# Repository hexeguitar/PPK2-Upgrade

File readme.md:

# PPK2 Logic Port upgrade
### Logic port upgrade add on for the Nordic Power Profiler Kit II.  

![alt text][img_features] 
![alt text][img_main] 

Copyright (c) 2022 by Piotr Zapart  
www.hexefx.com  

[img_features]: pics/ppk2_logicPortUpgrade_v2.jpg " Features" 
[img_main]: pics/ppk2lp_1.jpg "PPK2 Logic Port upgrade"

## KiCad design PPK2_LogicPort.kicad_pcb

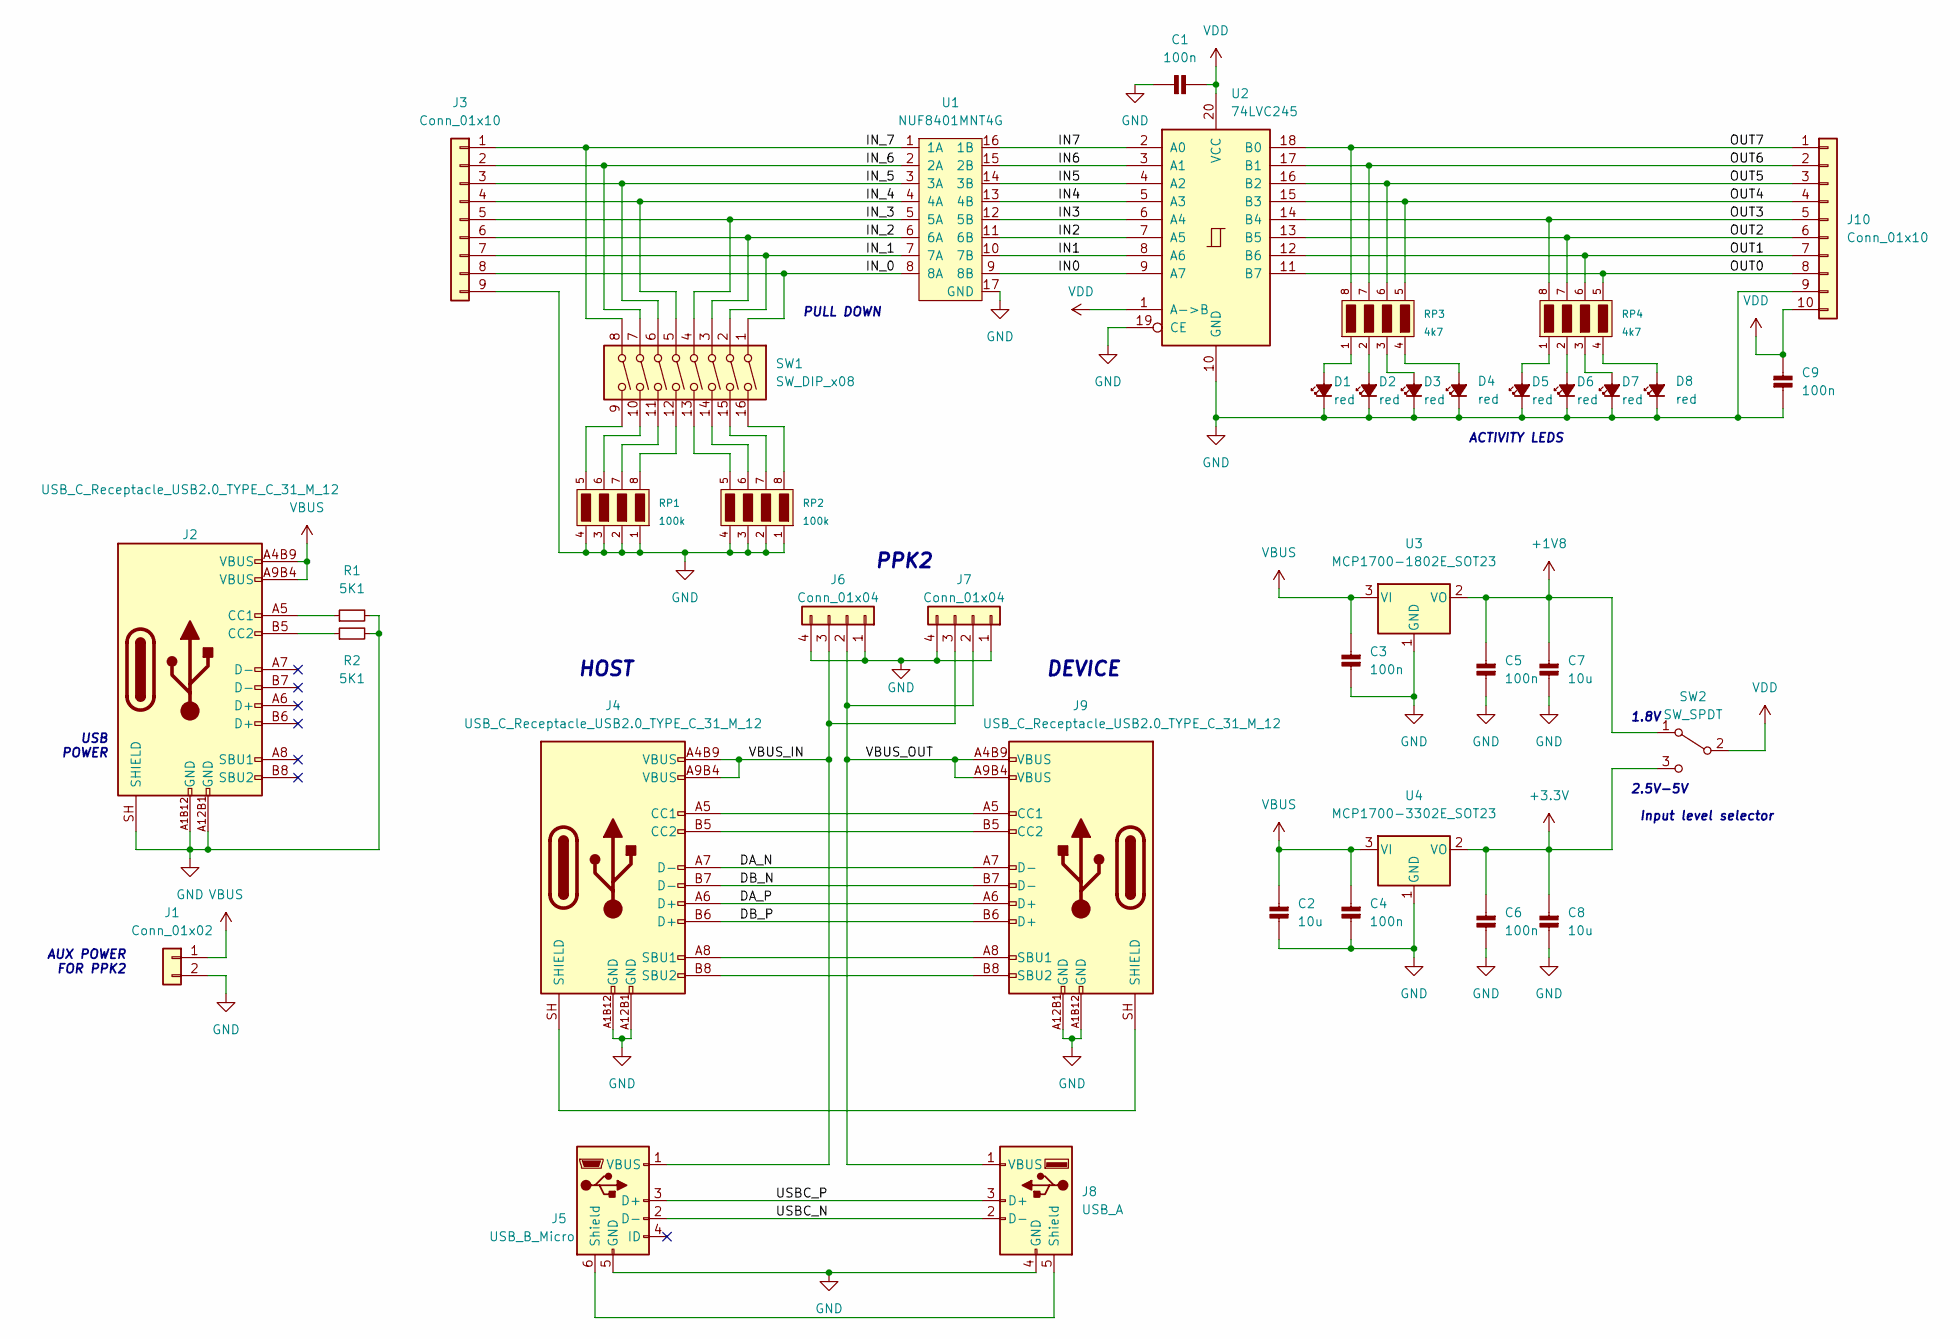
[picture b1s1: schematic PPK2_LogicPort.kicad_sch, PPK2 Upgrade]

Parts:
C1, C3, C4, C5, C6, C9: 100n; Hx_C_0603_1608Metric
C2, C7, C8: 10u; Hx_C_0805_2012Metric
D1, D2, D3, D4, D5, D6, D7, D8: red; LED_0603_1608Metric
J1: Conn_01x02; JST_PH_S2B-PH-SM4-TB_1x02-1MP_P2.00mm_Horizontal
J2, J4, J9: USB_C_Receptacle_USB2.0_TYPE_C_31_M_12; USB_C_TYPE-C-31-M-12; LCSC C283540
J3: Conn_01x10; PinHeader_1x09_P2.54mm_Horizontal
J5: USB_B_Micro; USB_Micro-B_Molex-105017-0001
J6: Conn_01x04; PinSocket_1x04_P2.54mm_Horizontal
J7: Conn_01x04; PinHeader_1x04_P2.54mm_Vertical
J8: USB_A; USB_A_Molex_67643_Horizontal
J10: Conn_01x10; PinSocket_1x10_P2.54mm_Horizontal
R1, R2: 5K1; Hx_R_0805_2012Metric
RP1, RP2: 100k; R_Array_Convex_4x0603
RP3, RP4: 4k7; R_Array_Convex_4x0603
SW1: SW_DIP_x08; SW_DIP_SPSTx08_Slide_9.78x22.5mm_W7.62mm_P2.54mm
SW2: SW_SPDT; SW_SPDT_PCM12
U1: NUF8401MNT4G; DFN-16-1EP_1.6x4mm_P0.5mm
U2: 74LVC245; TSSOP-20_4.4x6.5mm_Pitch0.65mm
U3: MCP1700-1802E_SOT23; SOT-23
U4: MCP1700-3302E_SOT23; SOT-23

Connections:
+1V8: C5.2, C7.2, SW2.1 (A), U3.2 (VO)
+3.3V: C6.2, C8.2, SW2.3 (C), U4.2 (VO)
/DA_N: J4.A7 (D-), J9.A7 (D-)
/DA_P: J4.A6 (D+), J9.A6 (D+)
/DB_N: J4.B7 (D-), J9.B7 (D-)
/DB_P: J4.B6 (D+), J9.B6 (D+)
/IN0: U1.9 (8B), U2.9 (A7)
/IN1: U1.10 (7B), U2.8 (A6)
/IN2: U1.11 (6B), U2.7 (A5)
/IN3: U1.12 (5B), U2.6 (A4)
/IN4: U1.13 (4B), U2.5 (A3)
/IN5: U1.14 (3B), U2.4 (A2)
/IN6: U1.15 (2B), U2.3 (A1)
/IN7: U1.16 (1B), U2.2 (A0)
/IN_0: J3.8, SW1.1, U1.8 (8A)
/IN_1: J3.7, SW1.2, U1.7 (7A)
/IN_2: J3.6, SW1.3, U1.6 (6A)
/IN_3: J3.5, SW1.4, U1.5 (5A)
/IN_4: J3.4, SW1.5, U1.4 (4A)
/IN_5: J3.3, SW1.6, U1.3 (3A)
/IN_6: J3.2, SW1.7, U1.2 (2A)
/IN_7: J3.1, SW1.8, U1.1 (1A)
/OUT0: J10.8, RP4.5 (R4), U2.11 (B7)
/OUT1: J10.7, RP4.6 (R3), U2.12 (B6)
/OUT2: J10.6, RP4.7 (R2), U2.13 (B5)
/OUT3: J10.5, RP4.8 (R1), U2.14 (B4)
/OUT4: J10.4, RP3.5 (R4), U2.15 (B3)
/OUT5: J10.3, RP3.6 (R3), U2.16 (B2)
/OUT6: J10.2, RP3.7 (R2), U2.17 (B1)
/OUT7: J10.1, RP3.8 (R1), U2.18 (B0)
/USBC_N: J5.2 (D-), J8.2 (D-)
/USBC_P: J5.3 (D+), J8.3 (D+)
/VBUS_IN: J4.A4B9 (VBUS), J4.A9B4 (VBUS), J5.1 (VBUS), J6.3, J7.3
/VBUS_OUT: J6.2, J7.2, J8.1 (VBUS), J9.A4B9 (VBUS), J9.A9B4 (VBUS)
unnamed: D1.2 (A), RP3.1
unnamed: D2.2 (A), RP3.2
unnamed: D3.2 (A), RP3.3
unnamed: D4.2 (A), RP3.4
unnamed: D5.2 (A), RP4.1
unnamed: D6.2 (A), RP4.2
unnamed: D7.2 (A), RP4.3
unnamed: D8.2 (A), RP4.4
unnamed: J2.A5 (CC1), R1.1
unnamed: J2.B5 (CC2), R2.1
unnamed: J4.A5 (CC1), J9.A5 (CC1)
unnamed: J4.A8 (SBU1), J9.A8 (SBU1)
unnamed: J4.B5 (CC2), J9.B5 (CC2)
unnamed: J4.B8 (SBU2), J9.B8 (SBU2)
unnamed: J4.SH (SHIELD), J9.SH (SHIELD)
unnamed: J5.6 (Shield), J8.5 (Shield)
unnamed: RP1.5 (R4), SW1.9
unnamed: RP1.6 (R3), SW1.10
unnamed: RP1.7 (R2), SW1.11
unnamed: RP1.8 (R1), SW1.12
unnamed: RP2.5 (R4), SW1.13
unnamed: RP2.6 (R3), SW1.14
unnamed: RP2.7 (R2), SW1.15
unnamed: RP2.8 (R1), SW1.16
VBUS: C2.2, C3.2, C4.2, J1.1, J2.A4B9 (VBUS), J2.A9B4 (VBUS), U3.3 (VI), U4.3 (VI)
VDD: C1.2, C9.1, J10.10, SW2.2 (B), U2.1 (A->B), U2.20 (VCC)

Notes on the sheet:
PPK2
USB POWER
AUX POWER FOR PPK2
2.5V-5V
HOST
PULL DOWN
1.8V
DEVICE
Input level selector
ACTIVITY LEDS

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
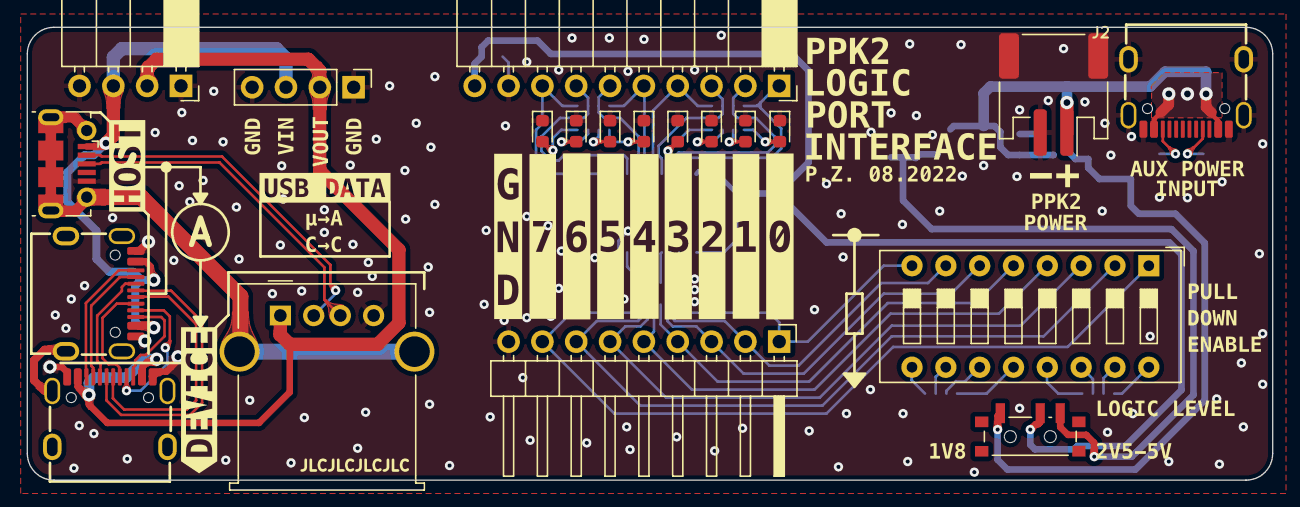
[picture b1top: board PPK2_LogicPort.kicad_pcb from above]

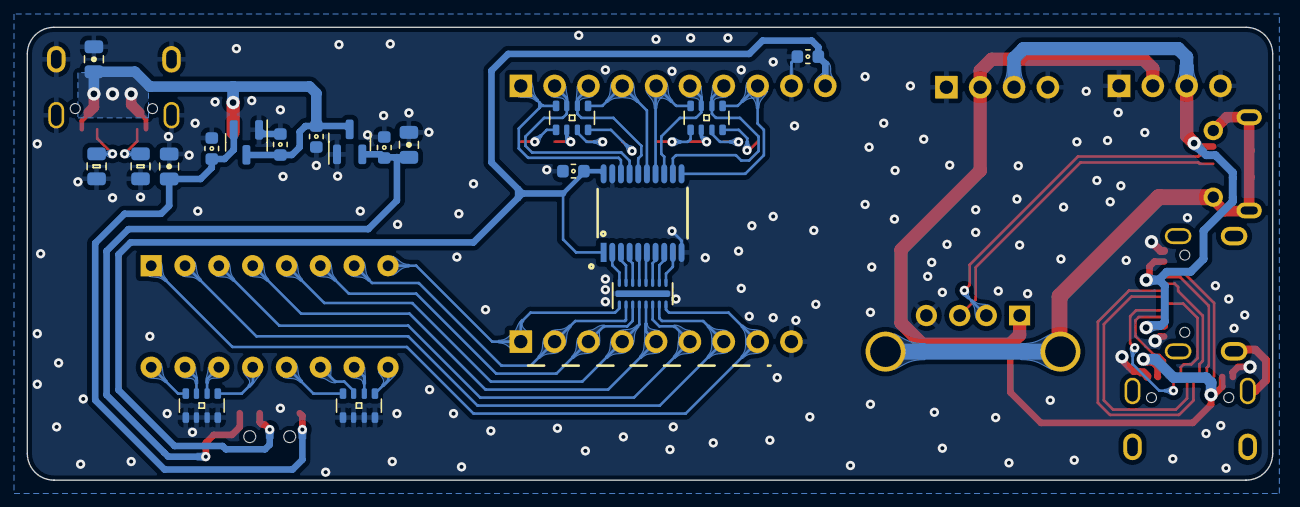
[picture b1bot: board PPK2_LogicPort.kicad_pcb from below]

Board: 2 copper layers, 93.5 x 34.0 mm, 71 parts (19 on the bottom side), 61 nets.

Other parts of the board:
kibuzzard-62F7C5A6: G***; kibuzzard-62F7C5A6
kibuzzard-62F7C5B3: G***; kibuzzard-62F7C5B3
kibuzzard-62F7C5FC: G***; kibuzzard-62F7C5FC
kibuzzard-62F7C55F: G***; kibuzzard-62F7C55F
kibuzzard-62F7C56D: G***; kibuzzard-62F7C56D
kibuzzard-62F7C58A: G***; kibuzzard-62F7C58A
kibuzzard-62F7C59B: G***; kibuzzard-62F7C59B
kibuzzard-62F7C566: G***; kibuzzard-62F7C566
kibuzzard-62F7C581: G***; kibuzzard-62F7C581
kibuzzard-62F7CD71: G***; kibuzzard-62F7CD71
kibuzzard-62F7CDBE: G***; kibuzzard-62F7CDBE
kibuzzard-62F7CDCB: G***; kibuzzard-62F7CDCB
kibuzzard-62F7CE01: G***; kibuzzard-62F7CE01
kibuzzard-62F7CE3D: G***; kibuzzard-62F7CE3D
kibuzzard-62F7CE10: G***; kibuzzard-62F7CE10
kibuzzard-62F7CFD5: G***; kibuzzard-62F7CFD5
kibuzzard-62F7CFF3: G***; kibuzzard-62F7CFF3
kibuzzard-62F7D7EA: G***; kibuzzard-62F7D7EA
kibuzzard-6303D62C, kibuzzard-6303D62C#2: G***; kibuzzard-6303D62C
kibuzzard-6303D65D: G***; kibuzzard-6303D65D
kibuzzard-6303D476: G***; kibuzzard-6303D476
kibuzzard-6303D495: G***; kibuzzard-6303D495
kibuzzard-6303D652: G***; kibuzzard-6303D652
kibuzzard-63012C63: G***; kibuzzard-63012C63
kibuzzard-63047CCA: G***; kibuzzard-63047CCA
kibuzzard-63047D09: G***; kibuzzard-63047D09
kibuzzard-630492D4: G***; kibuzzard-630492D4
kibuzzard-630727B6: G***; kibuzzard-630727B6
kibuzzard-630727C0: G***; kibuzzard-630727C0
kibuzzard-6304826C: G***; kibuzzard-6304826C
kibuzzard-63048273: G***; kibuzzard-63048273

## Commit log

2023-02-04 readme update
2023-02-04 add schematic pdf
2023-02-04 schematic update
